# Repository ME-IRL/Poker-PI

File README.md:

# Poker-π
Custom PCB for iKBC Poker II Mechanical Keyboard

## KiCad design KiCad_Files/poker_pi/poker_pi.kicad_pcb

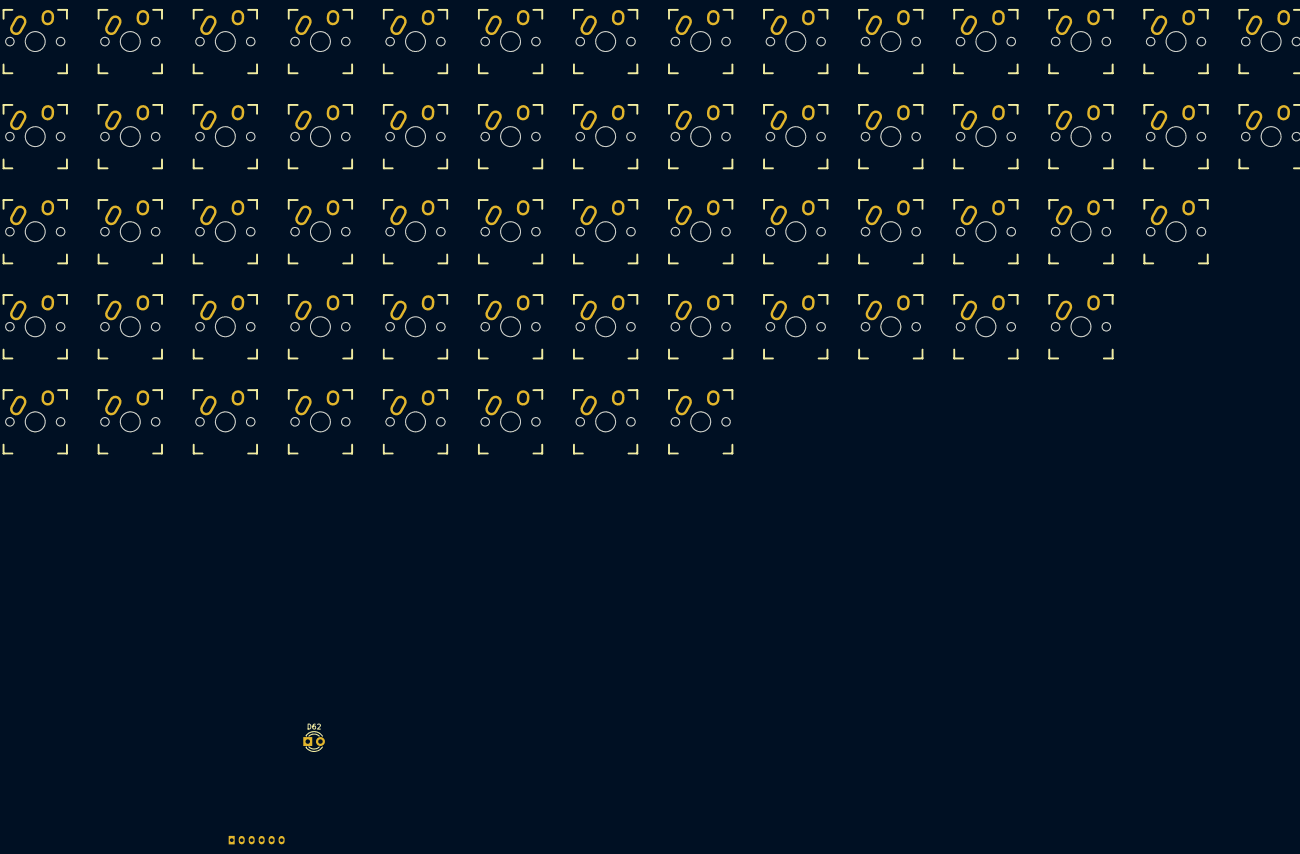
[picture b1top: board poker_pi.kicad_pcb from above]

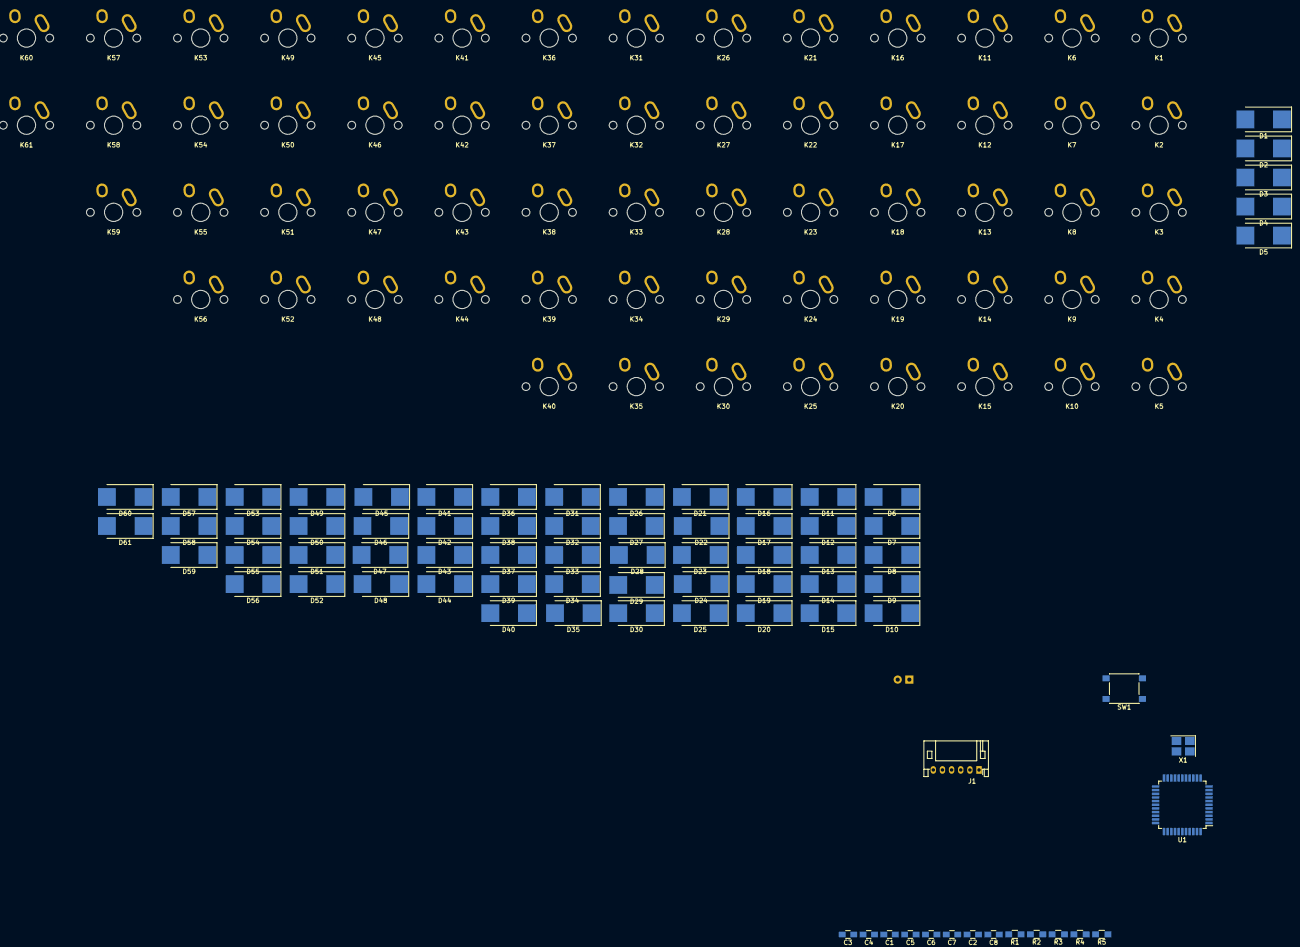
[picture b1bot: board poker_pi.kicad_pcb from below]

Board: 2 copper layers, 140 parts (78 on the bottom side), 93 nets, no tracks yet.

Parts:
C1, C2: 22pF; C_0805_HandSoldering
C3: 1uF; C_0805_HandSoldering
C4, C5, C6, C7: 0.1uF; C_0805_HandSoldering
C8: 4.7uF; C_0805_HandSoldering
D1, D2, D3, D4, D5, D6, D7, D8, D9, D10, D11, D12, D13, D14, D15, D16, D17, D18, D19, D20, D21, D22, D23, D24, D25, D26, D27, D28, D29, D30, D31, D32, D33, D34, D35, D36, D37, D38, D39, D40, D41, D42, D43, D44, D45, D46, D47, D48, D49, D50, D51, D52, D53, D54, D55, D56, D57, D58, D59, D60, D61: D; D_3220
D62: LED; LED_D3.0mm
J1: Conn_01x05; JST_PH_S6B-PH-K_06x2.00mm_Angled
K1, K2, K3, K4, K5, K6, K7, K8, K9, K10, K11, K12, K13, K14, K15, K16, K17, K18, K19, K20, K21, K22, K23, K24, K25, K26, K27, K28, K29, K30, K31, K32, K33, K34, K35, K36, K37, K38, K39, K40, K41, K42, K43, K44, K45, K46, K47, K48, K49, K50, K51, K52, K53, K54, K55, K56, K57, K58, K59, K60, K61: KEYSW; Mx_Alps_100
R1, R4: 10k; R_0805_HandSoldering
R2, R3: 22; R_0805_HandSoldering
R5: 470; R_0805_HandSoldering
SW1: SW_PUSH; SW_SPST_PTS645
U1: ATMEGA32U4; LQFP-44_10x10mm_Pitch0.8mm
X1: XTAL_GND; Crystal_SMD_3225-4pin_3.2x2.5mm_HandSoldering

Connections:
/col0: K1.1, K2.1, K3.1, K4.1, K5.1, U1.42
/col1: K6.1, K7.1, K8.1, K9.1, K10.1, U1.41
/col2: K11.1, K12.1, K13.1, K14.1, K15.1, U1.40
/col3: K16.1, K17.1, K18.1, K19.1, K20.1, U1.39
/col4: K21.1, K22.1, K23.1, K24.1, K25.1, U1.38
/col5: K26.1, K27.1, K28.1, K29.1, K30.1, U1.37
/col6: K31.1, K32.1, K33.1, K34.1, K35.1, U1.36
/col7: K36.1, K37.1, K38.1, K39.1, K40.1, U1.18
/col8: K41.1, K42.1, K43.1, K44.1, U1.19
/col9: K45.1, K46.1, K47.1, K48.1, U1.20
/col10: K49.1, K50.1, K51.1, K52.1, U1.21
/col11: K53.1, K54.1, K55.1, K56.1, U1.22
/col12: K57.1, K58.1, K59.1, U1.27
/col13: K60.1, K61.1, U1.26
/row0: D1.1, D6.1, D11.1, D16.1, D21.1, D26.1, D31.1, D36.1, D41.1, D45.1, D49.1, D53.1, D57.1, D60.1, U1.32
/row1: D2.1, D7.1, D12.1, D17.1, D22.1, D27.1, D32.1, D37.1, D42.1, D46.1, D50.1, D54.1, D58.1, D61.1, U1.31
/row2: D3.1, D8.1, D13.1, D18.1, D23.1, D28.1, D33.1, D38.1, D43.1, D47.1, D51.1, D55.1, D59.1, U1.30
/row3: D4.1, D9.1, D14.1, D19.1, D24.1, D29.1, D34.1, D39.1, D44.1, D48.1, D52.1, D56.1, U1.29
/row4: D5.1, D10.1, D15.1, D20.1, D25.1, D30.1, D35.1, D40.1, U1.28
GND: C1.2, C2.2, C3.2, C4.2, C5.2, C6.2, C7.2, C8.2, J1.2, J1.3, R4.1, R5.1, SW1.1, U1.5, U1.15, U1.23, U1.35, U1.43, X1.3
unnamed: C1.1, U1.16, X1.1
unnamed: C2.1, U1.17, X1.2
unnamed: C3.1, U1.6
unnamed: D1.2, K1.2
unnamed: D2.2, K2.2
unnamed: D3.2, K3.2
unnamed: D4.2, K4.2
unnamed: D5.2, K5.2
unnamed: D6.2, K6.2
unnamed: D7.2, K7.2
unnamed: D8.2, K8.2
unnamed: D9.2, K9.2
unnamed: D10.2, K10.2
unnamed: D11.2, K11.2
unnamed: D12.2, K12.2
unnamed: D13.2, K13.2
unnamed: D14.2, K14.2
unnamed: D15.2, K15.2
unnamed: D16.2, K16.2
unnamed: D17.2, K17.2
unnamed: D18.2, K18.2
unnamed: D19.2, K19.2
unnamed: D20.2, K20.2
unnamed: D21.2, K21.2
unnamed: D22.2, K22.2
unnamed: D23.2, K23.2
unnamed: D24.2, K24.2
unnamed: D25.2, K25.2
unnamed: D26.2, K26.2
unnamed: D27.2, K27.2
unnamed: D28.2, K28.2
unnamed: D29.2, K29.2
unnamed: D30.2, K30.2
unnamed: D31.2, K31.2
unnamed: D32.2, K32.2
unnamed: D33.2, K33.2
unnamed: D34.2, K34.2
unnamed: D35.2, K35.2
unnamed: D36.2, K36.2
unnamed: D37.2, K37.2
unnamed: D38.2, K38.2
unnamed: D39.2, K39.2
unnamed: D40.2, K40.2
unnamed: D41.2, K41.2
unnamed: D42.2, K42.2
unnamed: D43.2, K43.2
unnamed: D44.2, K44.2
unnamed: D45.2, K45.2
unnamed: D46.2, K46.2
unnamed: D47.2, K47.2
unnamed: D48.2, K48.2
unnamed: D49.2, K49.2
unnamed: D50.2, K50.2
unnamed: D51.2, K51.2
unnamed: D52.2, K52.2
unnamed: D53.2, K53.2
unnamed: D54.2, K54.2
unnamed: D55.2, K55.2
unnamed: D56.2, K56.2
unnamed: D57.2, K57.2
unnamed: D58.2, K58.2
unnamed: D59.2, K59.2
unnamed: D60.2, K60.2
unnamed: D61.2, K61.2
unnamed: D62.1, R5.2
unnamed: D62.2, U1.25
unnamed: J1.4, R2.2
unnamed: J1.5, R3.2
unnamed: R1.1, SW1.2, U1.13
unnamed: R2.1, U1.3
unnamed: R3.1, U1.4
unnamed: R4.2, U1.33
VCC: C4.1, C5.1, C6.1, C7.1, C8.1, J1.1, R1.2, U1.2, U1.7, U1.14, U1.24, U1.34, U1.44

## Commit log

2019-05-09 π
    πππ
2019-05-09 KiCad Setup
    Created project and added component symbol and footprint libraries
2019-05-11 Schematics Done Rev 1.0
2019-05-11 Footprints and USB connector
2019-05-11 Started layout
    Need to update diode footprints (to smaller)
    Spacing
    Crystal footprint pins
    Border edge cut
2019-05-14 Edge Cuts
    Drew edge cuts; check right most notch on the bottom
    Do other holes
    Fixed diode footprint
    Did top 3 rows. (Still gotta align last column)
    Put down 4th row; should be a bit lower
